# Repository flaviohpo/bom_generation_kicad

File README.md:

[Link para a versão original no notion](https://flaviohpo.notion.site/Boas-pr-ticas-para-gerar-BOM-no-KiCad-6-linux-b1b27ac0a2bf46eea822b32368cc44d1)

# Resumo

Neste artigo serão abordadas boas práticas para a geração do BOM utilizando o software KiCad 6.

O objetivo principal é reduzir o tempo de revisão e preparação do arquivo que é enviado para a cotação da PCB e montagem, além de enriquecer a documentação e diminuir a ocorrência de erros no BOM.

Para isto serão abordados os seguintes tópicos:

- Utilização de campos personalizados nos componentes.

- Edição do script de geração de BOM do próprio KiCad tornando possível a geração de BOM para variantes de montagem.

- Utilização do plugin InteractiveBOM.

Executando estas etapas durante o desenvolvimento, o projetista conseguirá obter um BOM confiável e uma excelente documentação para a montagem, com a possibilidade de prever variações na montagem.

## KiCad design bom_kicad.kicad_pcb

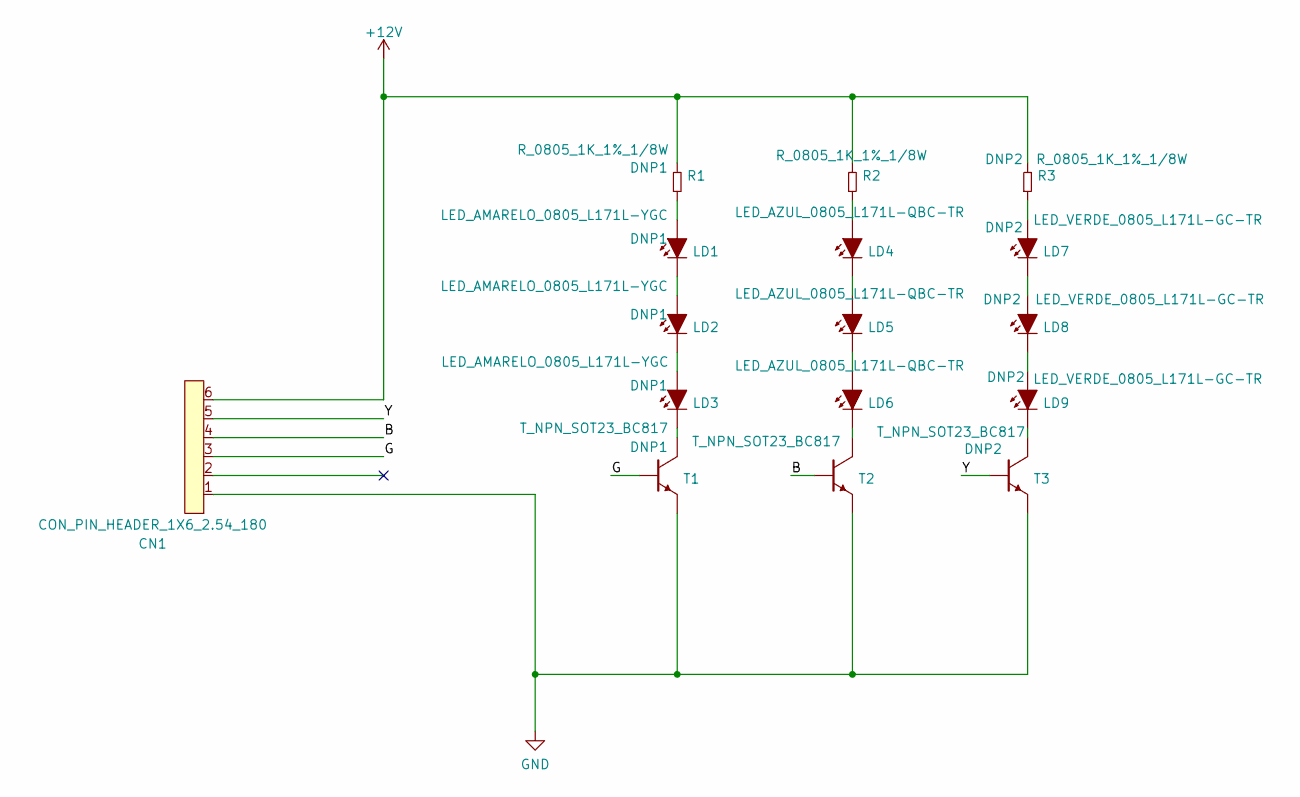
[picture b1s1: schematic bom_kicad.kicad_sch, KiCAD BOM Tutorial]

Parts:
CN1: CON_PIN_HEADER_1X6_2.54_180; pin_header_male_6_2.54_pth
LD1, LD2, LD3: LED_AMARELO_0805_L171L-YGC; LED_0805
LD4, LD5, LD6: LED_AZUL_0805_L171L-QBC-TR; LED_0805
LD7, LD8, LD9: LED_VERDE_0805_L171L-GC-TR; LED_0805
R1, R2, R3: R_0805_1K_1%_1/8W; RES_0805
T1, T2, T3: T_NPN_SOT23_BC817; SOT_23

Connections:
/B: CN1.4, T2.1 (B)
/G: CN1.3, T1.1 (B)
/Y: CN1.5, T3.1 (B)
unnamed: CN1.1, T1.2 (C), T2.2 (C), T3.2 (C)
unnamed: CN1.6, R1.2 (ANODE), R2.2 (ANODE), R3.2 (ANODE)
unnamed: LD1.1 (CATHODE), LD2.2 (ANODE)
unnamed: LD1.2 (ANODE), R1.1 (CATHODE)
unnamed: LD2.1 (CATHODE), LD3.2 (ANODE)
unnamed: LD3.1 (CATHODE), T1.3 (E)
unnamed: LD4.1 (CATHODE), LD5.2 (ANODE)
unnamed: LD4.2 (ANODE), R2.1 (CATHODE)
unnamed: LD5.1 (CATHODE), LD6.2 (ANODE)
unnamed: LD6.1 (CATHODE), T2.3 (E)
unnamed: LD7.1 (CATHODE), LD8.2 (ANODE)
unnamed: LD7.2 (ANODE), R3.1 (CATHODE)
unnamed: LD8.1 (CATHODE), LD9.2 (ANODE)
unnamed: LD9.1 (CATHODE), T3.3 (E)

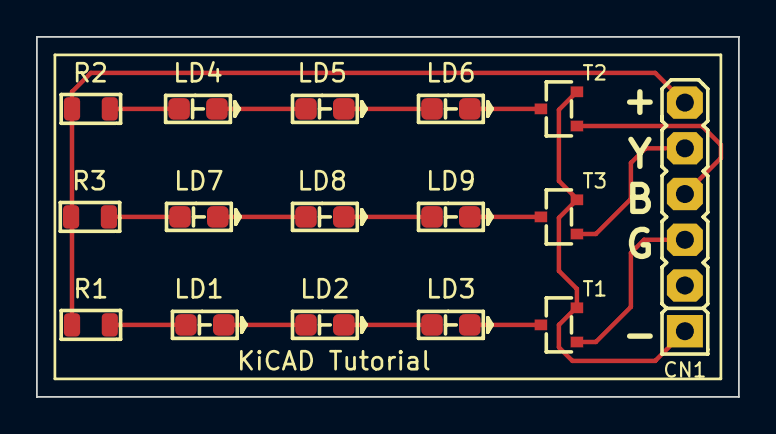
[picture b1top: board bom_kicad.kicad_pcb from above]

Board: 2 copper layers, 39.0 x 20.0 mm, 16 parts (0 on the bottom side), 17 nets.

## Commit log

2022-04-17 commit inicial
2022-04-17 adicionado pdf do artigo
2022-04-17 Update bom_csv_grouped_by_value_with_variation.py
    Removidos comentarios #flavio do script
